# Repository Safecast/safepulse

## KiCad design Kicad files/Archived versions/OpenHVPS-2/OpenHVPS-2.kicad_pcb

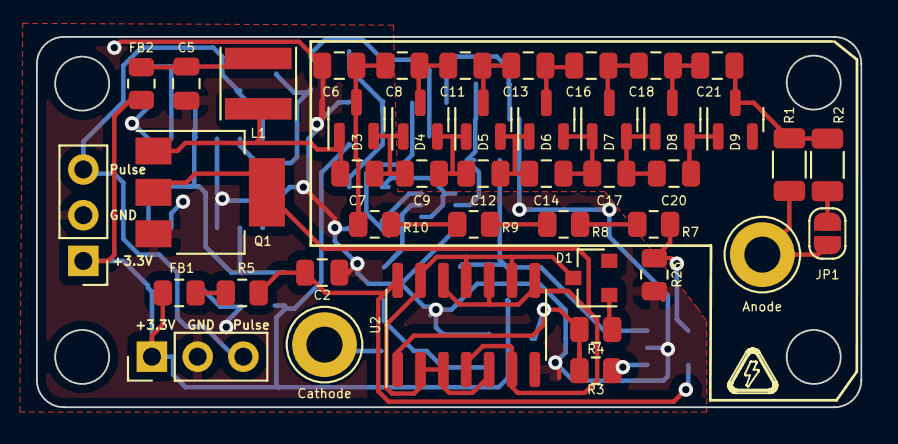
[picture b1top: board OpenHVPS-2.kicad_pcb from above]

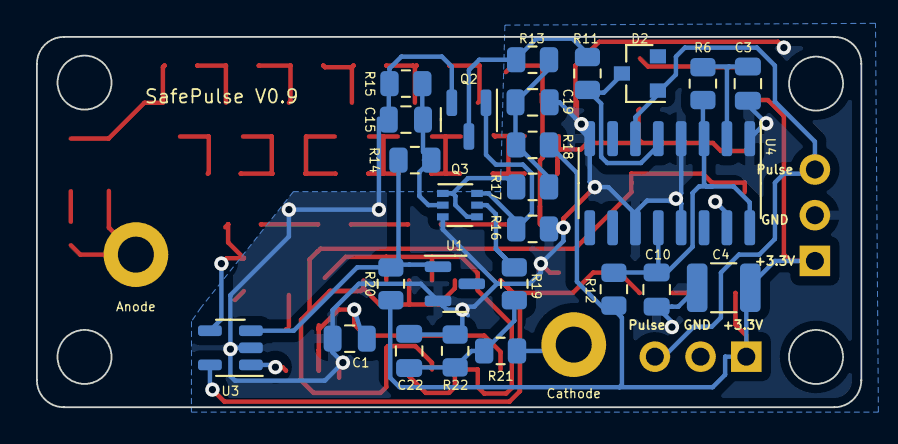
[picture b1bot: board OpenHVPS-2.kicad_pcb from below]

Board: 2 copper layers, 45.8 x 20.6 mm, 69 parts (26 on the bottom side), 43 nets.

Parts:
C1: 150pF; C_0805_2012Metric
C2, C5, C10: 1uF; C_0805_2012Metric
C3, C15, C22: 1nF; C_0805_2012Metric
C4: 10uF; C_1210_3225Metric
C6, C7, C8, C9, C11, C12, C13, C14, C16, C17, C18, C19, C20, C21: 0.1uF; C_0805_2012Metric
D1, D2: BAS16; D_SOT-23_ANK
D3, D4, D5, D6, D7, D8, D9: BAV23; SOT-23
FB1, FB2: BKP2125HS221-T; R_0805_2012Metric
H1: Cathode; TestPoint_Loop_D3.80mm_Drill2.0mm
H2: Anode; TestPoint_Loop_D3.80mm_Drill2.0mm
J1, J2: Conn_01x03_Male; PinHeader_1x03_P2.54mm_Vertical
JP1: 7317; SolderJumper-2_P1.3mm_Open_RoundedPad1.0x1.5mm
L1: NRS6020T2R2NMGJ; L_Taiyo-Yuden_MD-4040
Q1: FQT7N10; SOT-223-3_TabPin2
Q2: BC846A; SOT-23
Q3: MMDT3906; SOT-363_SC-70-6
R1, R2: 10M; R_1206_3216Metric
R3, R4: 100K; R_0805_2012Metric
R5, R12: 100; R_0805_2012Metric
R6: 121k; R_0805_2012Metric
R7, R8, R9, R10: 22M; R_0805_2012Metric
R11: 33k; R_0805_2012Metric
R13, R19: 100k; R_0805_2012Metric
R14: 1M5; R_0805_2012Metric
R15: 392k; R_0805_2012Metric
R16: 1M; R_0805_2012Metric
R17: 499k; R_0805_2012Metric
R18: 1k; R_0805_2012Metric
R20: 560K; R_0805_2012Metric
R21: 47k; R_0805_2012Metric
R22: 20k; R_0805_2012Metric
R23: 3.16M; R_0805_2012Metric
U1: MAX6008AEUR+T; SOT-23
U2: 74HC14; SOIC-14_3.9x8.7mm_P1.27mm
U3: MAX4162; SOT-23-5
U4: CD14538BM; SOIC-16_3.9x9.9mm_P1.27mm

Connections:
+2V5: R14.1, R20.2, U1.1 (IN), U3.3 (+)
+3V3: C4.1, FB1.1, FB2.1, J1.1, J2.1, R12.1, R18.2, R20.1
GND: C1.2, C2.2, C3.2, C4.2, C5.2, C6.1, C10.2, C15.2, C19.2, C22.2, J1.2, J2.2, Q1.3 (S), Q2.2 (E), Q3.3 (C2), R15.2, R16.2, R22.2, R23.2, U1.2 (OUT), U2.7 (GND), U3.2 (V-), U4.1 (VSS), U4.4 (Clk+), U4.8 (VSS), U4.11 (Clk-), U4.13 (R), U4.15 (VSS)
unnamed: C1.1, R3.1, R4.1, U2.1
unnamed: C3.1, R6.2, U4.2 (RxCx)
unnamed: C5.1, FB2.2, L1.1
unnamed: C6.2, C8.1, D3.3 (K), R10.1
unnamed: C7.1, D3.1 (K), L1.2, Q1.1 (D)
unnamed: C7.2, C9.1, D3.2 (A), D4.1 (K)
unnamed: C10.1, R6.1, R12.2, U4.3 (R), U4.12 (Clk+), U4.16 (VDD)
unnamed: C8.2, C11.1, D4.3 (K)
unnamed: C11.2, C13.1, D5.3 (K)
unnamed: C9.2, C12.1, D4.2 (A), D5.1 (K)
unnamed: C12.2, C14.1, D5.2 (A), D6.1 (K)
unnamed: C13.2, C16.1, D6.3 (K)
unnamed: C14.2, C17.1, D6.2 (A), D7.1 (K)
unnamed: C15.1, Q3.2 (B1), R14.2, R15.1
unnamed: C16.2, C18.1, D7.3 (K)
unnamed: C17.2, C20.1, D7.2 (A), D8.1 (K)
unnamed: C18.2, C21.1, D8.3 (K)
unnamed: C19.1, R13.1, R17.1, R18.1
unnamed: C20.2, D8.2 (A), D9.1 (K)
unnamed: C21.2, D9.3 (K), R1.1, R2.1
unnamed: C22.1, R19.2, R21.2, R22.1
unnamed: D1.1 (K), U2.2, U2.3, U2.5, U2.9, U2.11, U2.13
unnamed: D1.2 (A), R4.2
unnamed: D2.1 (K), R11.1, U4.5 (Clk-)
unnamed: D2.2 (A), J1.3, J2.3, U4.6 (Q)
unnamed: FB1.2, R5.2
unnamed: H1.1, R21.1
unnamed: H2.1, JP1.2 (B), R1.2
unnamed: JP1.1 (A), R2.2
unnamed: Q1.2 (G), U2.4, U2.6, U2.8, U2.10, U2.12
unnamed: Q2.1 (B), Q3.6 (C1), R16.1
unnamed: Q2.3 (C), R11.2, R13.2
unnamed: Q3.1 (E1), Q3.4 (E2), R17.2
unnamed: Q3.5 (B2), R19.1
unnamed: R3.2, U3.1
unnamed: R7.2, R8.1
unnamed: R8.2, R9.1
unnamed: R9.2, R10.2
unnamed: R7.1, R23.1, U3.4 (-)
unnamed: C2.1, R5.1, U2.14 (VCC), U3.5 (V+)

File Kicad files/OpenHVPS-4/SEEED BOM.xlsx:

Designator | MPN/Seeed SKU | Qty | Link | value
C1 | Capacitor_SMD:C_0805_2012Metric | 1 | https://www.digikey.com/en/products/detail/w%C3%BCrth-elektr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 | 150pF
C2, C5, C10 | Capacitor_SMD:C_0805_2012Metric | 3 | https://www.digikey.com/en/products/detail/samsung-electro-m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 | 1uF
C3, C15 | Capacitor_SMD:C_0805_2012Metric | 2 | https://www.digikey.com/en/products/detail/tdk-corporation/C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 | 1nF
C4 | Capacitor_SMD:C_1210_3225Metric | 1 | https://www.digikey.com/en/products/detail/taiyo-yuden/EMK32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 | 10uF
C6, C7, C8, C9, C11, C12, C13, C14, C16, C17, C18, C19, C20, C21 | Capacitor_SMD:C_0805_2012Metric | 14 | https://www.digikey.com/en/products/detail/tdk-corporation/C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 | 0.1uF
C22 | Capacitor_SMD:C_0805_2012Metric | 1 | https://www.digikey.com/en/products/detail/kemet/C0805C361J1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 | 360pF
D1, D2 | Diode_SMD:D_SOT-23_ANK | 2 | https://www.vishay.com/docs/85748/1n4148w.pdf | BAS16
D3, D4, D5, D6, D7, D8, D9 | Package_TO_SOT_SMD:SOT-23 | 7 | https://www.digikey.com/en/products/detail/tdk-corporation/C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 | BAV23
FB1, FB2 | Resistor_SMD:R_0805_2012Metric | 2 | https://www.digikey.com/en/products/detail/taiyo-yuden/BKP21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 | BKP2125HS221-T
H1 | TestPoint:TestPoint_Loop_D3.80mm_Drill2.0mm | 1 | ~ | Cathode
H2 | TestPoint:TestPoint_Loop_D3.80mm_Drill2.0mm | 1 | ~ | Anode
J1, J2 | Connector_PinHeader_2.54mm:PinHeader_1x03_P2.54mm_Vertical | 2 | ~ | Conn_01x03_Male
JP1 | Jumper:SolderJumper-2_P1.3mm_Open_RoundedPad1.0x1.5mm | 1 | ~ | 7317
L1 | Inductor_SMD:L_Taiyo-Yuden_MD-4040 | 1 | https://www.digikey.com/en/products/detail/taiyo-yuden/NRS60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 | NRS6020T2R2NMGJ
Q1 | Package_TO_SOT_SMD:SOT-223-3_TabPin2 | 1 | https://www.digikey.com/en/products/detail/on-semiconductor/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 | FQT7N10
Q2 | Package_TO_SOT_SMD:SOT-23 | 1 | https://www.digikey.com/en/products/detail/diodes-incorporat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 | BC846A
Q3 | Package_TO_SOT_SMD:SOT-363_SC-70-6 | 1 | https://www.digikey.com/en/products/detail/diodes-incorporat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 | MMDT3906
R1, R2 | Resistor_SMD:R_1206_3216Metric | 2 | https://www.digikey.com/en/products/detail/yageo/RC1206FR-07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 | 10M
R3, R4 | Resistor_SMD:R_0805_2012Metric | 2 | https://www.digikey.com/en/products/detail/stackpole-electro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 | 100K
R5, R12 | Resistor_SMD:R_0805_2012Metric | 2 | https://www.digikey.com/en/products/detail/te-connectivity-p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 | 100
R6 | Resistor_SMD:R_0805_2012Metric | 1 | https://www.digikey.com/en/products/detail/koa-speer-electro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 | 121k
R7, R8, R9, R10 | Resistor_SMD:R_0805_2012Metric | 4 | https://www.digikey.com/en/products/detail/stackpole-electro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 | 22M
R11 | Resistor_SMD:R_0805_2012Metric | 1 | https://www.digikey.com/en/products/detail/te-connectivity-p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 | 33k
R13, R19 | Resistor_SMD:R_0805_2012Metric | 2 | https://www.digikey.com/en/products/detail/stackpole-electro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 | 100k
R14 | Resistor_SMD:R_0805_2012Metric | 1 | https://www.digikey.com/en/products/detail/vishay-dale/CRCW0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 | 1M5
R15 | Resistor_SMD:R_0805_2012Metric | 1 | https://www.digikey.com/en/products/detail/yageo/RC0805FR-07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 | 392k
R16 | Resistor_SMD:R_0805_2012Metric | 1 | https://www.digikey.com/en/products/detail/yageo/RT0805FRE07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 | 1M
R17 | Resistor_SMD:R_0805_2012Metric | 1 | https://www.digikey.com/en/products/detail/stackpole-electro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 | 499k
R18 | Resistor_SMD:R_0805_2012Metric | 1 | https://www.digikey.com/en/products/detail/yageo/RT0805FRE07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 | 1k
R20 | Resistor_SMD:R_0805_2012Metric | 1 | https://www.digikey.com/en/products/detail/yageo/RT0805FRE07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 | 560K
R21 | Resistor_SMD:R_0805_2012Metric | 1 | https://www.digikey.com/en/products/detail/yageo/RC0805FR-07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 | 47k
R22 | Resistor_SMD:R_0805_2012Metric | 1 | https://www.digikey.com/en/products/detail/panasonic-electro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 | 20k
R23 | Resistor_SMD:R_0805_2012Metric | 1 | https://www.digikey.com/en/products/detail/yageo/RC0805FR-07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 | 3.16M
U1 | Package_TO_SOT_SMD:SOT-23 | 1 | https://www.digikey.com/en/products/detail/maxim-integrated/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 | MAX6008AEUR+T
U2 | Package_SO:SOIC-14_3.9x8.7mm_P1.27mm | 1 | https://www.digikey.com/en/products/detail/texas-instruments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 | 74HC14
U3 | Package_TO_SOT_SMD:SOT-23-5 | 1 | http://www.ti.com/lit/ds/symlink/tlv2375.pdf | MAX4162
U4 | Package_SO:SOIC-16_3.9x9.9mm_P1.27mm | 1 | https://assets.nexperia.com/documents/data-sheet/HEF4538B.pdf | CD14538BM

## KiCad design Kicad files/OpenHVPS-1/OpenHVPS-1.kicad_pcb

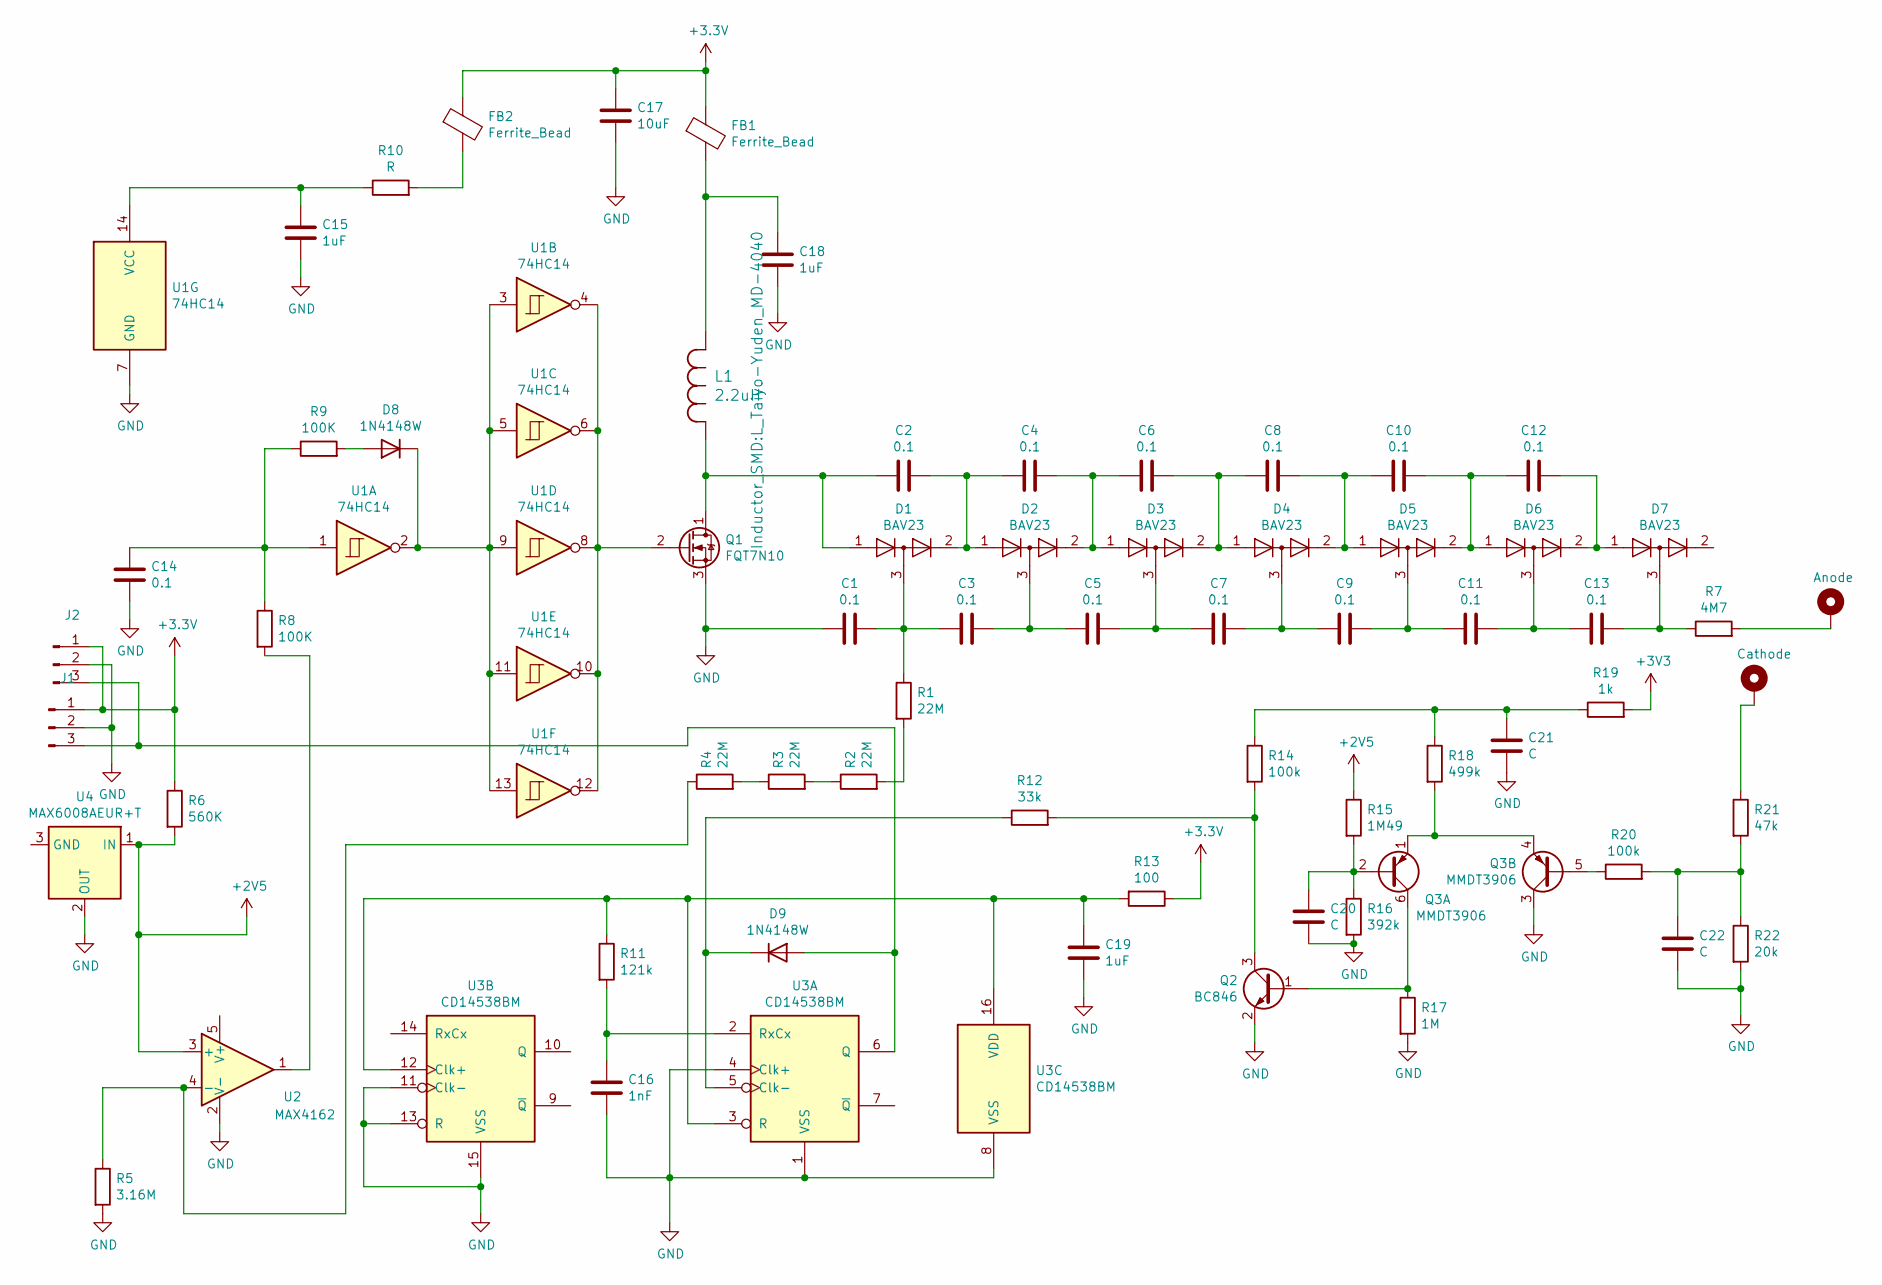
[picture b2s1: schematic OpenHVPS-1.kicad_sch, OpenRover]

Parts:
C1, C2, C3, C4, C5, C6, C7, C8, C9, C10, C11, C12, C13: 0.1; R_0805_2012Metric
C14: 0.1; C_0805_2012Metric
C15, C18, C19: 1uF; C_0805_2012Metric
C16: 1nF; C_0805_2012Metric
C17: 10uF; C_1210_3225Metric
C20, C21, C22: C; C_0805_2012Metric
D1, D2, D3, D4, D5, D6, D7: BAV23; SOT-23
D8, D9: 1N4148W; D_SOD-123
FB1, FB2: Ferrite_Bead; R_0805_2012Metric
H2: Cathode; TestPoint_Loop_D3.80mm_Drill2.0mm
H5: Anode; TestPoint_Loop_D3.80mm_Drill2.0mm
J1, J2: Conn_01x03_Male; PinHeader_1x03_P2.54mm_Vertical
L1: 2.2uH; L_Taiyo-Yuden_MD-4040
Q1: FQT7N10; SOT-223-3_TabPin2
Q2: BC846; SOT-23
Q3: MMDT3906; SOT-363_SC-70-6
R1, R2, R3, R4: 22M; R_0805_2012Metric
R5: 3.16M; R_0805_2012Metric
R6: 560K; R_0805_2012Metric
R7: 4M7; R_1206_3216Metric
R8, R9: 100K; R_0805_2012Metric
R10: R; R_0805_2012Metric
R11: 121k; R_0805_2012Metric
R12: 33k; R_0805_2012Metric
R13: 100; R_0805_2012Metric
R14, R20: 100k; R_0805_2012Metric
R15: 1M49; R_0805_2012Metric
R16: 392k; R_0805_2012Metric
R17: 1M; R_0805_2012Metric
R18: 499k; R_0805_2012Metric
R19: 1k; R_0805_2012Metric
R21: 47k; R_0805_2012Metric
R22: 20k; R_0805_2012Metric
U1: 74HC14; SOIC-14_3.9x8.7mm_P1.27mm
U2: MAX4162; SOT-23-5
U3: CD14538BM; SOIC-16_3.9x9.9mm_P1.27mm
U4: MAX6008AEUR+T; SOT-23

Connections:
+2V5: R6.2, R15.1, U2.3 (+), U4.1 (IN)
GND: C1.1, C14.2, C15.2, C16.2, C17.2, C18.2, C19.2, C20.2, C21.2, C22.2, J1.2, J2.2, Q1.3 (S), Q2.2 (E), Q3.3 (C2), R5.2, R16.2, R17.2, R22.2, U1.7 (GND), U2.2 (V-), U3.1 (VSS), U3.4 (Clk+), U3.8 (VSS), U3.11 (Clk-), U3.13 (R), U3.15 (VSS), U4.2 (OUT)
unnamed: C1.2, C3.1, D1.3 (K), R1.1
unnamed: C2.1, D1.1 (K), L1.2, Q1.1 (D)
unnamed: C2.2, C4.1, D1.2 (A), D2.1 (K)
unnamed: C3.2, C5.1, D2.3 (K)
unnamed: C4.2, C6.1, D2.2 (A), D3.1 (K)
unnamed: C5.2, C7.1, D3.3 (K)
unnamed: C6.2, C8.1, D3.2 (A), D4.1 (K)
unnamed: C7.2, C9.1, D4.3 (K)
unnamed: C8.2, C10.1, D4.2 (A), D5.1 (K)
unnamed: C10.2, C12.1, D5.2 (A), D6.1 (K)
unnamed: C9.2, C11.1, D5.3 (K)
unnamed: C11.2, C13.1, D6.3 (K)
unnamed: C12.2, D6.2 (A), D7.1 (K)
unnamed: C13.2, D7.3 (K), R7.1
unnamed: C14.1, R8.1, R9.1, U1.1
unnamed: C15.1, R10.1, U1.14 (VCC)
unnamed: C16.1, R11.2, U3.2 (RxCx)
unnamed: C18.1, FB1.2, L1.1
unnamed: C19.1, R11.1, R13.2, U3.3 (R), U3.12 (Clk+), U3.16 (VDD)
unnamed: C20.1, Q3.2 (B1), R15.2, R16.1
unnamed: C21.1, R14.1, R18.1, R19.1
unnamed: C22.1, R20.2, R21.2, R22.1
unnamed: D8.1 (K), U1.2, U1.3, U1.5, U1.9, U1.11, U1.13
unnamed: D8.2 (A), R9.2
unnamed: D9.1 (K), R12.1, U3.5 (Clk-)
unnamed: D9.2 (A), J1.3, J2.3, U3.6 (Q)
unnamed: FB2.2, R10.2
unnamed: H2.1, R21.1
unnamed: H5.1, R7.2
unnamed: Q1.2 (G), U1.4, U1.6, U1.8, U1.10, U1.12
unnamed: Q2.1 (B), Q3.6 (C1), R17.1
unnamed: Q2.3 (C), R12.2, R14.2
unnamed: Q3.1 (E1), Q3.4 (E2), R18.2
unnamed: Q3.5 (B2), R20.1
unnamed: R1.2, R2.2
unnamed: R2.1, R3.2
unnamed: R3.1, R4.2
unnamed: R4.1, R5.1, U2.4 (-)
unnamed: R8.2, U2.1

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
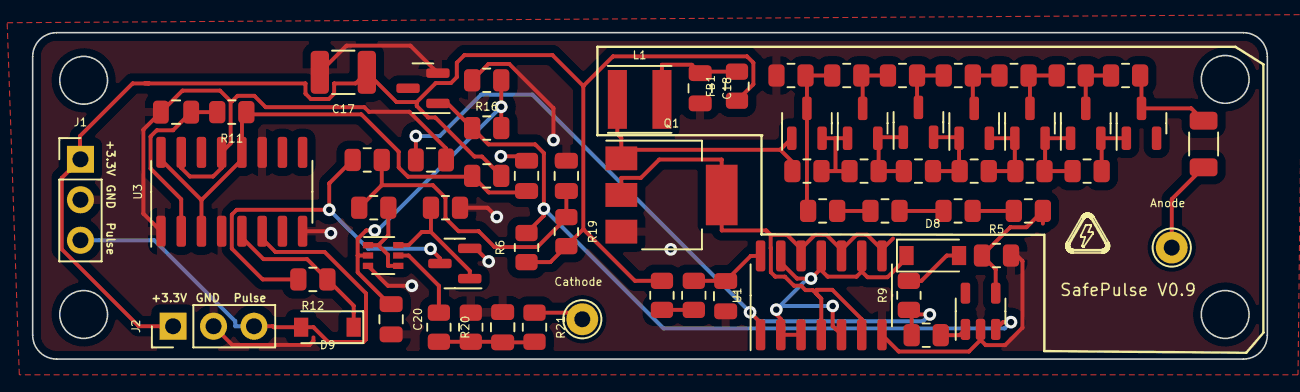
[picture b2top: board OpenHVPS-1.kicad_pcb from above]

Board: 2 copper layers, 77.5 x 20.5 mm, 67 parts (0 on the bottom side), 42 nets.

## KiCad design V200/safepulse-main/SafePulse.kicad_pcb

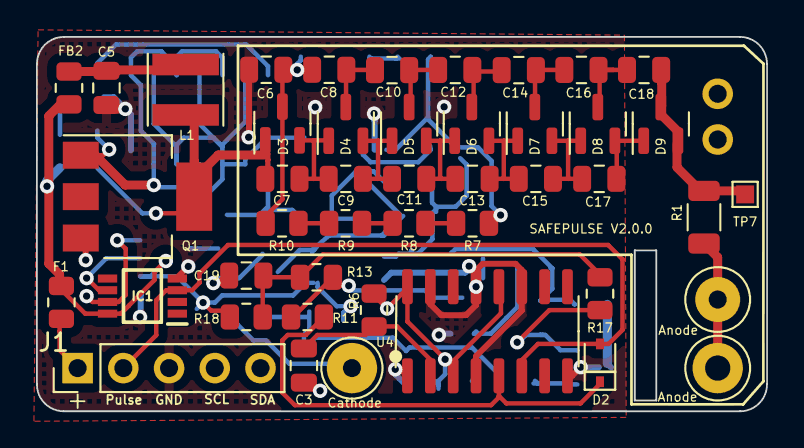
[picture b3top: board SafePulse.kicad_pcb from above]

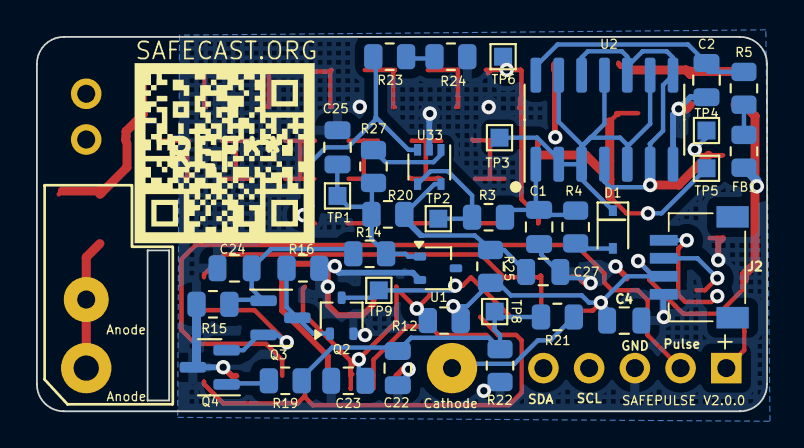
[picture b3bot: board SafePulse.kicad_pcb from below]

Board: 4 copper layers, 40.6 x 20.8 mm, 86 parts (40 on the bottom side), 48 nets.

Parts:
C1: 150pF; C_0805_2012Metric
C2, C4, C5, C19, C23, C27: 10uF; C_0805_2012Metric
C3, C24: 10nF; C_0805_2012Metric
C6, C7, C8, C9, C10, C11, C12, C13, C14, C15, C16, C17, C18: 0.1uF; C_0805_2012Metric
C22: 1.5nF; C_0805_2012Metric
C25: 2.2uF; C_0805_2012Metric
D1, D2: BAS16J; D_SOD-323
D3, D4, D5, D6, D7, D8, D9: BAV23S; SOT-23
F1: Polyfuse; R_0805_2012Metric
FB1, FB2: 74279220321; R_0805_2012Metric
H1: Cathode; TestPoint_Loop_D2.60mm_Drill1.4mm_Beaded
H2, H4: Anode; TestPoint_Loop_D3.50mm_Drill1.4mm_Beaded
IC1: S-35770E01I-K8T2U; SOP65P400X80-8N
J1: Conn_01x03_Male; PinHeader_1x05_P2.54mm_Vertical
J2: 4208
L1: 4.7uH; L_Taiyo-Yuden_MD-4040
Q1: FQT7N10L; SOT-223-3_TabPin4
Q2: BC846A; SOT-323_SC-70
Q3, Q4: MMBT3906; SOT-23
R1: 4.99M; R_1206_3216Metric
R3: 100K; R_0805_2012Metric
R4: 10K; R_0805_2012Metric
R5, R12, R25: 100; R_0805_2012Metric
R6: 121k; R_0805_2012Metric
R7, R8, R9, R10: 22M; R_0805_2012Metric
R11: 33k; R_0805_2012Metric
R13, R19: 100k; R_0805_2012Metric
R14: 357k; R_0805_2012Metric
R15: 220k; R_0805_2012Metric
R16: 1M; R_0805_2012Metric
R17: 499k; R_0805_2012Metric
R18: 1k; R_0805_2012Metric
R20: 118K; R_0805_2012Metric
R21: 47k; R_0805_2012Metric
R22: 12K; R_0805_2012Metric
R23, R27: 1.54M; R_0805_2012Metric
R24: 22k; R_0805_2012Metric
TP1, TP2, TP3, TP4, TP5, TP6, TP7, TP8, TP9: TestPoint; TestPoint_Pad_1.0x1.0mm
U1: TS4061AICT-1.25; SOT-323_SC-70
U2: 74HC14; SOIC-14_3.9x8.7mm_P1.27mm
U4: CD14538BM; SOIC-16_3.9x9.9mm_P1.27mm
U33: MAX9910EXK+T; SOT-353_SC-70-5
two_pinheader1: Conn_01x03_Male; PinHeader_1x02_P2.54mm_Vertical

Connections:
+1V2: C25.1, R14.1, R20.2, R27.2, TP1.1, U1.1 (IN)
+3V3: C4.1, F1.2, FB1.1, FB2.1, IC1.8 (VDD), J2.2, R12.1, R18.2, R25.1
GND: C1.2, C2.2, C3.2, C4.2, C5.2, C6.1, C19.2, C22.2, C23.2, C24.2, C25.2, C27.2, IC1.4 (VSS), J1.3, J2.1, Q1.3 (S), Q2.2 (E), Q4.3 (C), R15.2, R16.2, R22.2, R24.2, U1.2 (OUT), U2.7 (GND), U4.1 (VSS), U4.4 (Clk+), U4.8 (VSS), U4.11 (Clk-), U4.13 (R), U4.15 (VSS), U33.2 (V-)
unnamed: C1.1, R3.1, R4.1, U2.1
unnamed: C5.1, FB2.2, L1.1
unnamed: C6.2, C8.1, D3.3 (K), R10.1, TP6.1
unnamed: C8.2, C10.1, D4.3 (K)
unnamed: C10.2, C12.1, D5.3 (K)
unnamed: C12.2, C14.1, D6.3 (K)
unnamed: C14.2, C16.1, D7.3 (K)
unnamed: C16.2, C18.1, D8.3 (K)
unnamed: C19.1, R13.1, R17.1, R18.1
unnamed: C22.1, R19.2, R21.2, R22.1, TP8.1
unnamed: D1.2 (A), R4.2
unnamed: D1.1 (K), TP3.1, U2.2, U2.3, U2.5, U2.9, U2.11, U2.13
unnamed: D2.2 (A), IC1.3 (CLKIN), J1.2, U4.6 (Q)
unnamed: D2.1 (K), R11.1, U4.5 (Clk-)
unnamed: C7.2, C9.1, D3.2 (A), D4.1 (K)
unnamed: C9.2, C11.1, D4.2 (A), D5.1 (K)
unnamed: C11.2, C13.1, D5.2 (A), D6.1 (K)
unnamed: C13.2, C15.1, D6.2 (A), D7.1 (K)
unnamed: C15.2, C17.1, D7.2 (A), D8.1 (K)
unnamed: C17.2, D8.2 (A), D9.1 (K)
unnamed: C18.2, D9.2 (A), D9.3 (K), R1.1, TP7.1
unnamed: FB1.2, R5.2
unnamed: H1.1, R21.1
unnamed: H2.1, H4.1, R1.2
unnamed: IC1.7 (SCL), J1.4, J2.4
unnamed: IC1.6 (SDA), J1.5, J2.3
unnamed: F1.1, J1.1
unnamed: C7.1, D3.1 (K), L1.2, Q1.4 (D), TP5.1
unnamed: Q1.1 (G), TP4.1, U2.4, U2.6, U2.8, U2.10, U2.12
unnamed: Q2.1 (B), Q3.3 (C), R16.1
unnamed: Q2.3 (C), R11.2, R13.2, TP9.1
unnamed: C24.1, Q3.1 (B), R14.2, R15.1
unnamed: Q3.2 (E), Q4.2 (E), R17.2
unnamed: Q4.1 (B), R19.1
unnamed: R3.2, TP2.1, U33.4
unnamed: R7.2, R8.1
unnamed: R8.2, R9.1
unnamed: R9.2, R10.2
unnamed: R23.2, R24.1
unnamed: C2.1, R5.1, U2.14 (VCC)
unnamed: C23.1, R6.1, R12.2, U4.3 (R), U4.12 (Clk+), U4.16 (VDD)
unnamed: C3.1, R6.2, U4.2 (RxCx)
unnamed: R27.1, U33.1 (+)
unnamed: R7.1, R23.1, U33.3 (-)
unnamed: C27.1, R20.1, R25.2, U33.5 (V+)
